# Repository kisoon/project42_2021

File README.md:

# project42_2021
42보드 지원 문서에 오신 것을 환영합니다! 여기에서 사용 방법에 대한 정보를 찾을 수 있습니다.<br>
프로젝트 42 피지컬 컴퓨팅 키트 <a href=https://github.com/kisoon/project42_2021> 온라인 자료(깃허브)</a>

-- <a href = https://github.com/kisoon/project42_2021#-%EC%84%A4%EC%B9%98-%EB%B0%A9%EB%B2%95-> 보드 설치방법 </a><br>
-- <a href = https://github.com/kisoon/project42_2021/blob/main/README.md#-%EB%9D%BC%EC%9D%B4%EB%B8%8C%EB%9F%AC%EB%A6%AC-%EC%84%A4%EC%B9%98-%EB%B0%A9%EB%B2%95->라이브러리 설치 방법 </a> <br>
-- <a href = https://github.com/kisoon/project42_2021/blob/main/5-2.%20%ED%95%A8%EA%BB%98%20%EC%82%AC%EC%9A%A9%ED%95%98%EA%B8%B0.md> 함께사용하기 </a>

<H3> 보드 설치 방법 </h3>
1. 아두이노 프로그램을 설치해주세요. https://www.arduino.cc/en/software 다음 링크에서 자신의 컴퓨터OS환경에 맞는 버전을 다운로드 받으면 됩니다.<br>

2. 아두이노 프로그램을 실행시키고 환경설정 윈도우를 열어주세요.<br>
   win:파일->환경설정(Ctrl+,) / mac:arduino->preference(Command+,)<br>
   
3. 그리고 사진의 주황색 칸에 다음 링크를 복사하여 붙여넣고 확인버튼(OK)을 눌러주세요
   https://raw.githubusercontent.com/espressif/arduino-esp32/gh-pages/package_esp32_index.json<br>
4. 아두이노에서 보드 매니저를 실행하세요. 도구(Tools) 메뉴 -> Board -> 보드 매니저(Board Manager)
<br>
5. 보드 매니저를 실행 후 esp32 라고 검색을 해주세요. 그리고, <b>1.0.6버전</b>을 선택하고, 설치(instll)버튼을 클릭하여 esp32 보드를 아두이노에 설치합니다.

6. 그리고 아두이노 IDE를 다시 실행시키세요.

7. 다시! 도구(Tools) 메뉴 -> Board에서 ESP32 Arduino -> ESP32 Dev Module을 선택합니다.
  
8. 마지막으로 자신의 컴퓨터의 설치된 42보드 포트를 선택해야합니다. 포트를 선택하기전 컴퓨터에 드라이버 소프트웨어를 설치합니다.
   42보드에는 cp2104라는 USB포트 인식 칩이 내장되어 있습니다.
   다음 링크에서 자신의 컴퓨터 환경에 맞는 드라이버를 다운받아 설치합니다.
   https://www.silabs.com/developers/usb-to-uart-bridge-vcp-drivers

9. 드라이버의 설치를 완료한 뒤 다시 아두이노 IDE로 돌아와 도구(Tools) 메뉴에서 port를 확인합니다. 42보드를 USB케이블로 컴퓨터와 연결하면, 자신의 컴퓨터에 설치된 42보드 포트를 확인할 수 있습니다.
    windows는 COM[숫자]의 형태로 되어있습니다.

10. 42보드를 사용할 때는 항상 보드이름과 포트를 확인 후 사용합니다.

<H3> 라이브러리 설치 방법 </h3>
아두이노 라이브러리 설치 가이드 -> https://www.arduino.cc/en/Guide/Libraries

1. 라이브러리는 아두이노 IDE를 실행하여 설치할 수 있다.<br>
2. 스케치 메뉴 -> 라이브러리 포함하기(include library) -> Manage libraries를 선택한다.<br>

3. 검색창에 다음 라이브러리를 검색한 후 모두 설치를 한다.
   1) Adafruit_MPR121
   2) MPU6050 by electronic cats https://github.com/electroniccats/mpu6050
   3) Adafruit neopixel https://github.com/adafruit/Adafruit_NeoPixel
4. 다운받은 폴더의 libraries안의 AsyncTCP 폴더와 ESPAsyncWebServer 폴더를 <br>문서 -> arduino -> libraries 폴더안에 붙여넣기 합니다.<br>

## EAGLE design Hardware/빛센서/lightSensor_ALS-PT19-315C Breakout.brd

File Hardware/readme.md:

1. 42키트는 오픈소스를 활용해 만들었습니다.
2. autodesk eagle cad를 이용해 하드웨어를 디자인하였습니다.
3. https://www.autodesk.com/products/eagle/overview

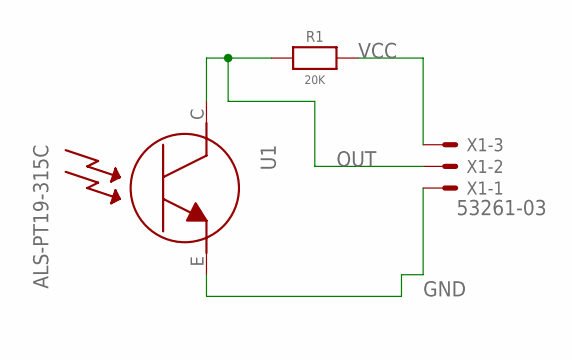
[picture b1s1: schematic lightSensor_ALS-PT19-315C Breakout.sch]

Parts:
R1: 20K; 0603-NO
U1: ALS-PT19-315C
X1: 53261-03

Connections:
GND: U1.E, X1.1
OUT: R1.2, U1.C, X1.2
VCC: R1.1, X1.3

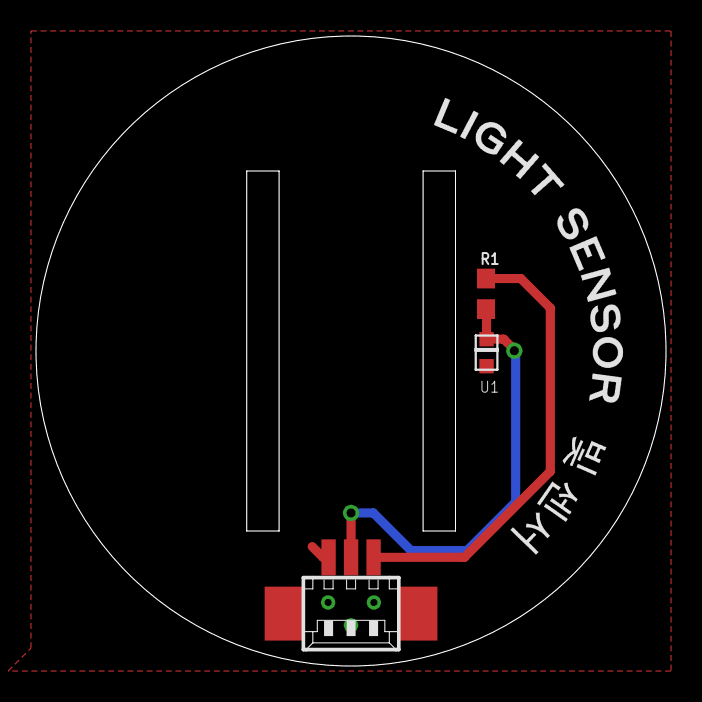
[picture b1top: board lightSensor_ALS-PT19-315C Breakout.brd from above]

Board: 2 copper layers, 35.0 x 35.0 mm, 3 parts (0 on the bottom side), 3 nets.

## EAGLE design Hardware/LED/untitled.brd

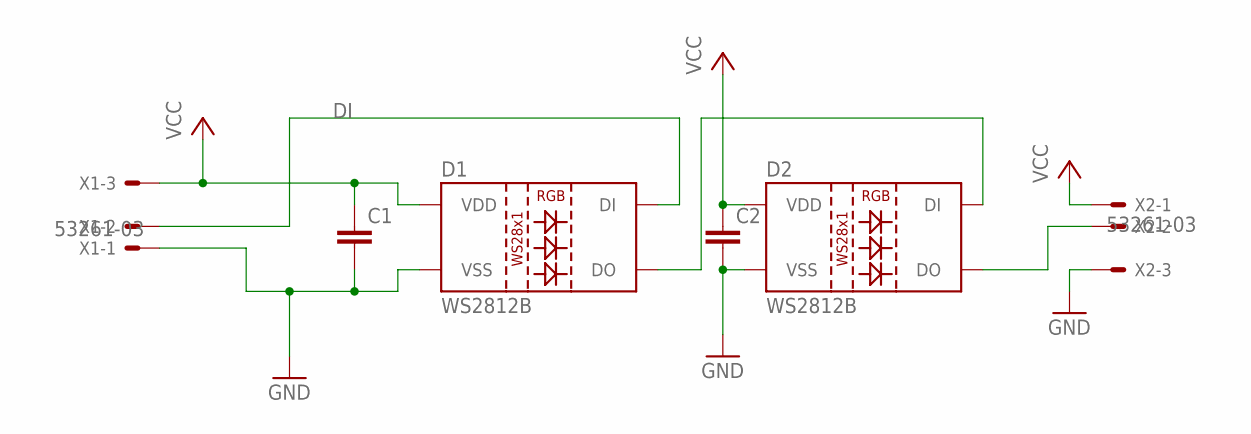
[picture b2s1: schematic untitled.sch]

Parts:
C1, C2: C-EUC0603; C0603
D1, D2: WS2812B
X1, X2: 53261-03

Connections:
DI: D1.4 (DI), X1.2
GND: C1.2, C2.2, D1.3 (VSS), D2.3 (VSS), X1.1, X2.3
unnamed: D2.2 (DO), X2.2
unnamed: D1.2 (DO), D2.4 (DI)
VCC: C1.1, C2.1, D1.1 (VDD), D2.1 (VDD), X1.3, X2.1

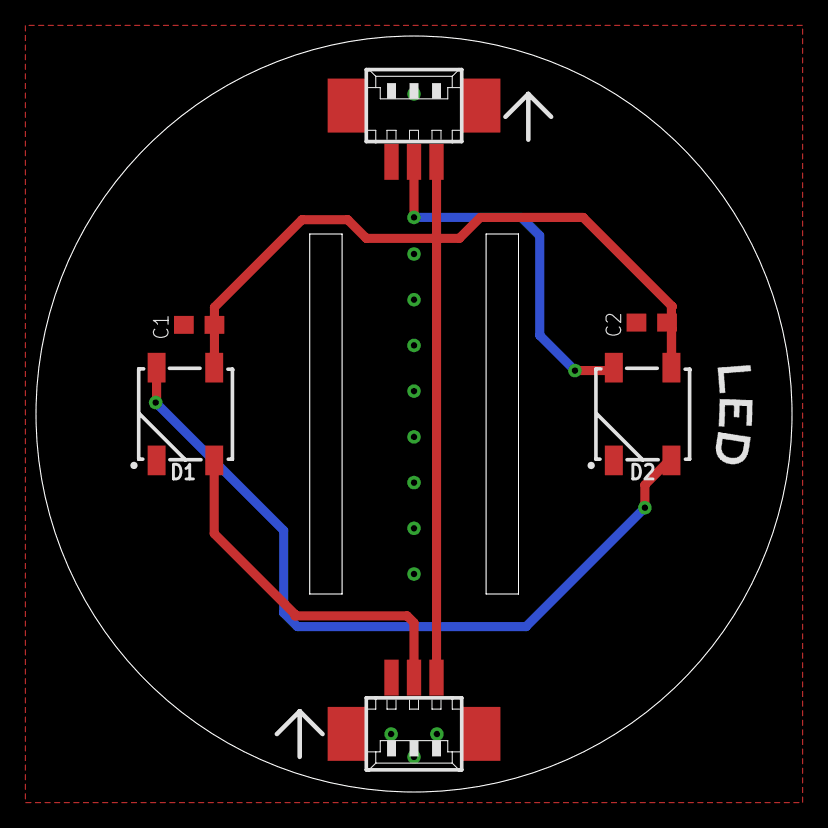
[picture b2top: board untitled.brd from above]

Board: 2 copper layers, 42.0 x 42.0 mm, 6 parts (0 on the bottom side), 5 nets.

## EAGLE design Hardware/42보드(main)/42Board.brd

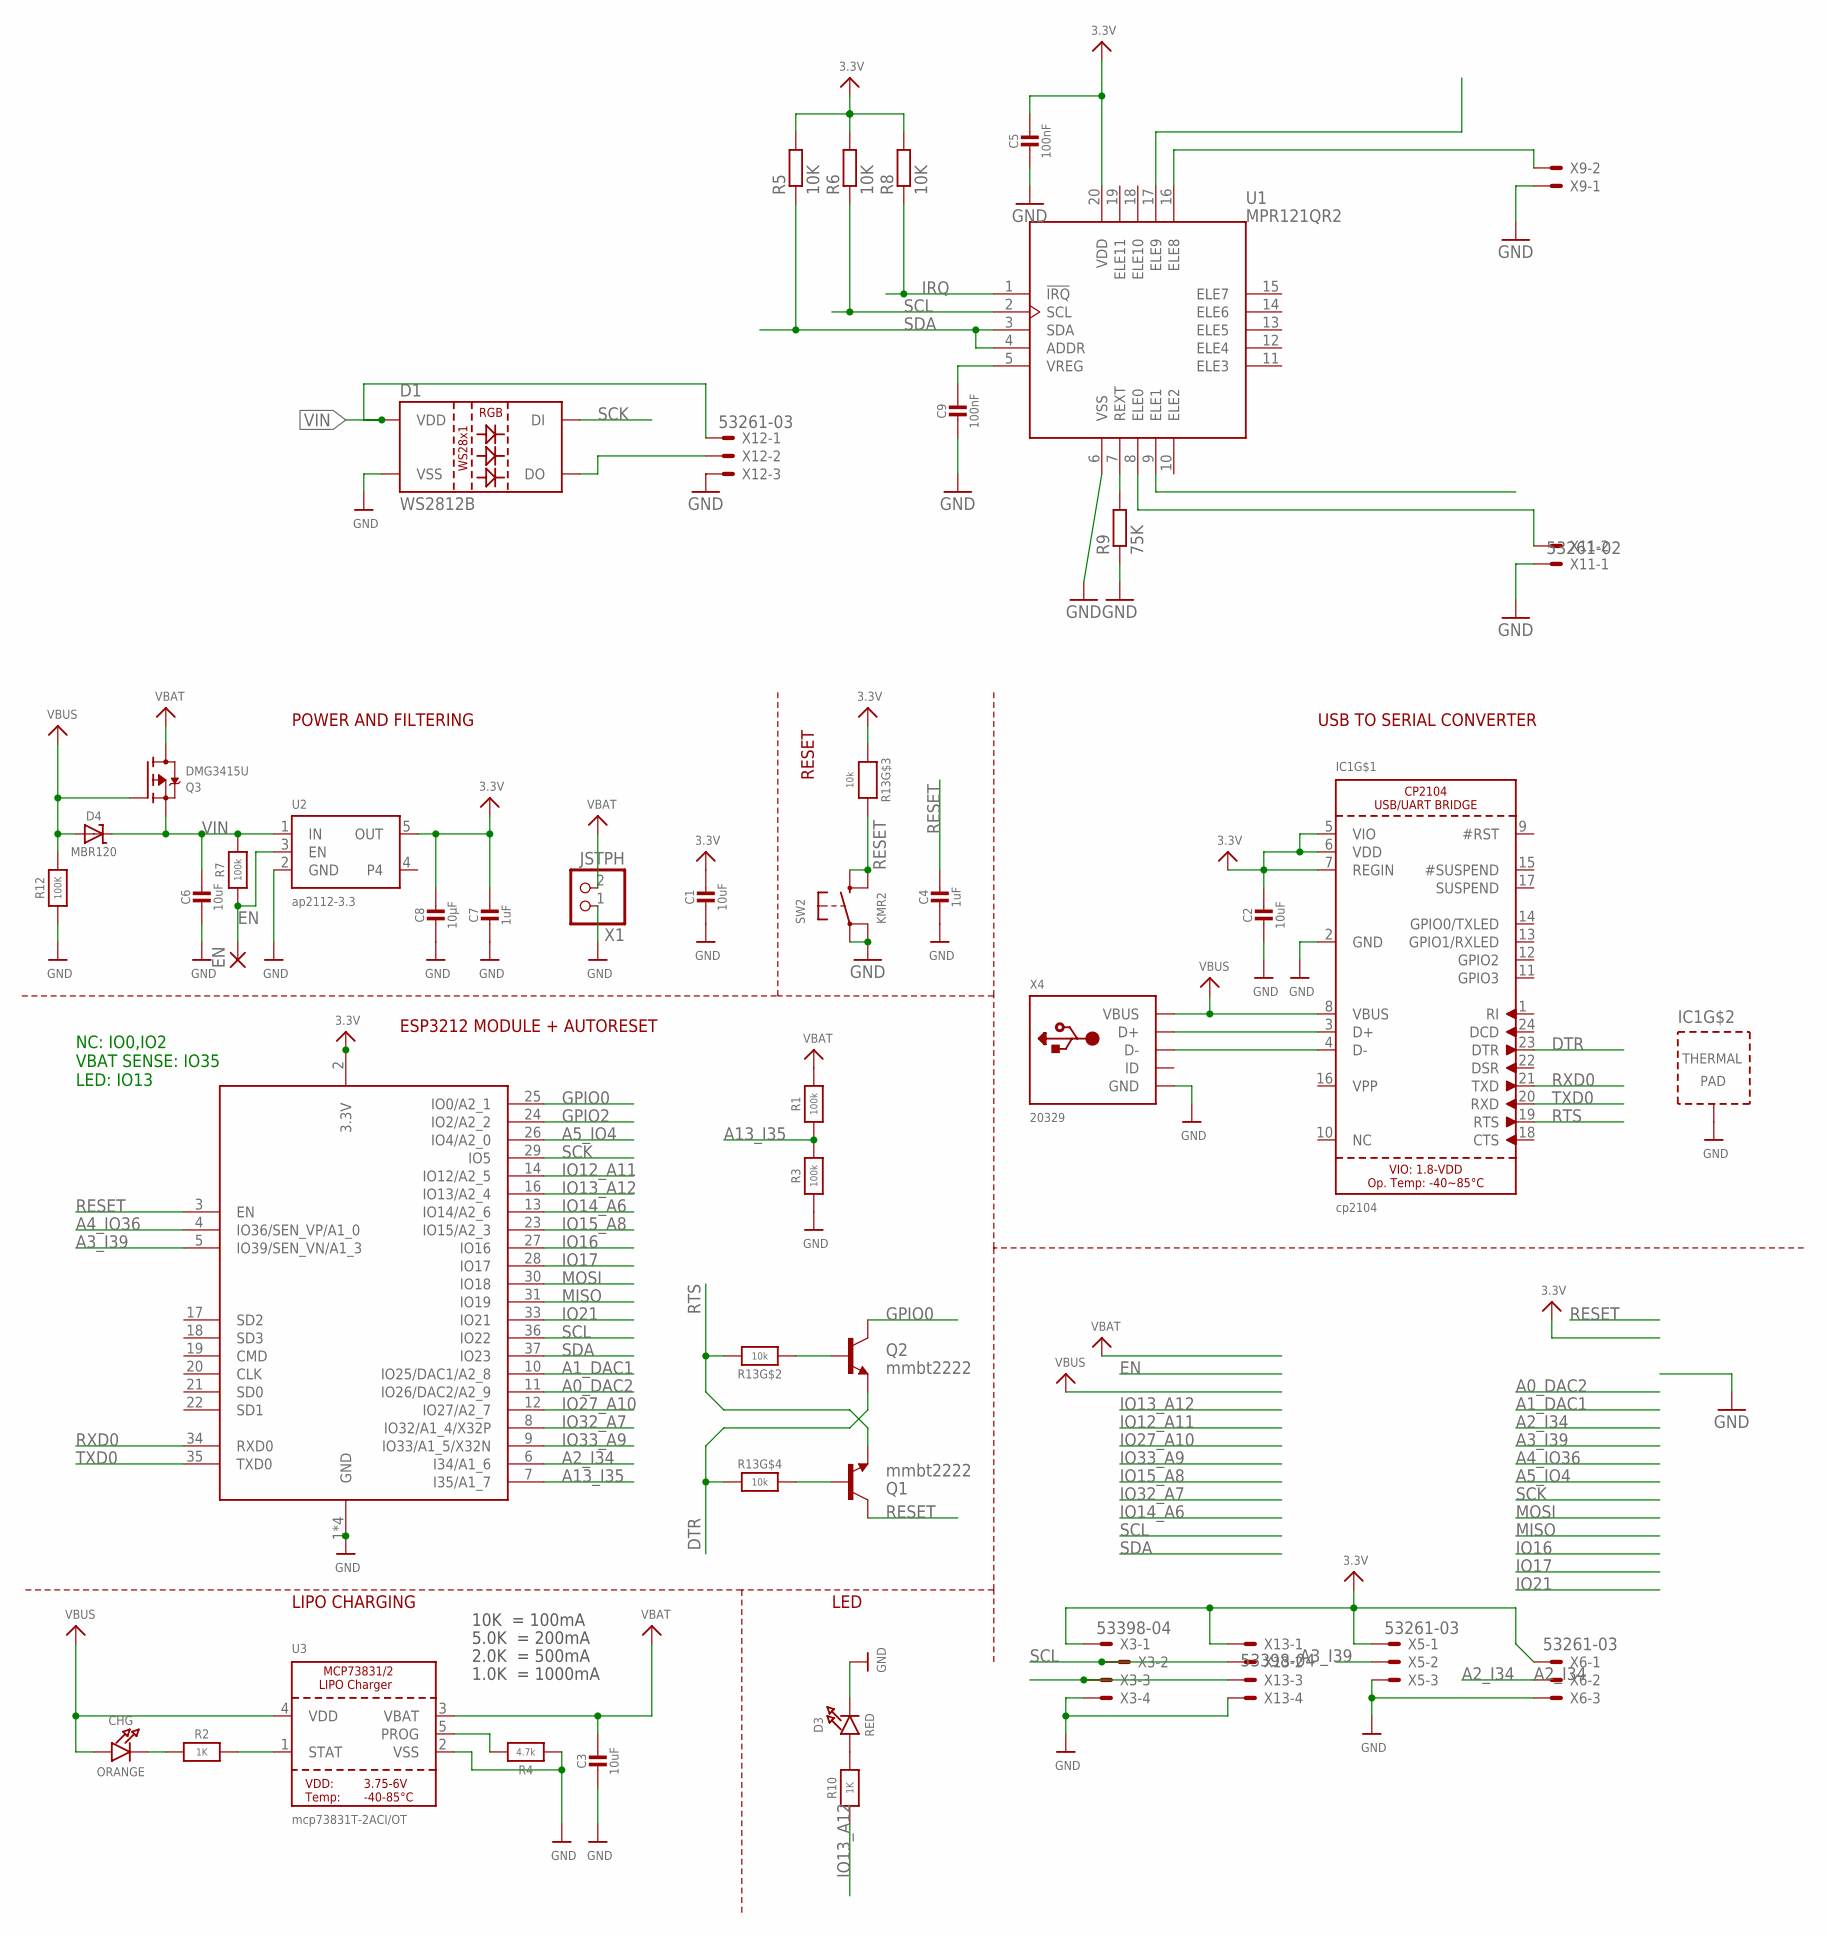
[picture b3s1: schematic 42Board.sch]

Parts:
C1, C2, C3, C6: 10uF; 0805-NO
C4, C7: 1uF; 0603-NO
C5, C9: 100nF; 0603-NO
C8: 10µF; 0805-NO
CHG: ORANGE; CHIPLED_0805_NOOUTLINE
D1: WS2812B
D3: RED; CHIPLED_0805_NOOUTLINE
D4: MBR120; SOD-123
EN: 1,6/0,8
IC1: cp2104; QFN24_4MM_SMSC
Q1, Q2: mmbt2222; SOT23-3
Q3: DMG3415U; SOT23-R
R1, R3, R7: 100k; 0603-NO
R2, R10: 1K; 0603-NO
R4: 4.7k; 0603-NO
R5, R6, R8: 10K; R0603
R9: 75K; R0603
R12: 100K; 0603-NO
R13: 10k; RESPACK_4X0603
SW2: KMR2; BTN_KMR2_4.6X2.8
U1: MPR121QR2; UFQFN-20
U2: ap2112-3.3; SOT23-5
U3: mcp73831T-2ACI/OT; SOT23-5
X1: JSTPH; JSTPH2
X2: ESP32_WROOM32_SKINNY; WROOM32_SKINNY
X3, X13: 53398-04
X4: 20329; 4UCONN_20329_V2
X5, X6, X12: 53261-03
X9, X11: 53261-02

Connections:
3.3V: C1.1, C2.1, C5.1, C7.1, C8.1, IC1.5 (VIO), IC1.6 (VDD), IC1.7 (REGIN), R5.2, R6.2, R8.2, R13.3 (1), U1.20 (VDD), U2.5 (OUT), X2.2 (3.3V), X3.1, X5.1, X6.1, X13.1
A0_DAC2: X2.11 (IO26/DAC2/A2_9)
A1_DAC1: X2.10 (IO25/DAC1/A2_8)
A2_I34: X2.6 (I34/A1_6), X6.2
A3_I39: X2.5 (IO39/SEN_VN/A1_3), X5.2
A4_IO36: X2.4 (IO36/SEN_VP/A1_0)
A5_IO4: X2.26 (IO4/A2_0)
A13_I35: R1.1, R3.2, X2.7 (I35/A1_7)
DTR: IC1.23 (DTR), Q2.2 (E), R13.4 (1)
EN: EN.1, R7.1, U2.3 (EN)
GND: C1.2, C2.2, C3.2, C4.2, C5.2, C6.2, C7.2, C8.2, C9.2, D1.3 (VSS), D3.C, IC1.2 (GND), IC1.THERM (TP), R3.1, R4.1, R9.1, R12.1, SW2.A, SW2.A' (P1), U1.6 (VSS), U2.2 (GND), U3.2 (VSS), X1.1, X2.1 (GND), X2.15 (GND), X2.38 (GND), X2.P$1 (GND), X3.4, X4.BASE@1 (GND), X4.BASE@2 (GND), X4.GND, X4.SPRT@1 (GND), X4.SPRT@2 (GND), X4.SPRT@3 (GND), X4.SPRT@4 (GND), X5.3, X6.3, X9.1, X11.1, X12.3, X13.4
GPIO0: Q2.3 (C), X2.25 (IO0/A2_1)
GPIO2: X2.24 (IO2/A2_2)
IO12_A11: X2.14 (IO12/A2_5)
IO13_A12: R10.1, X2.16 (IO13/A2_4)
IO14_A6: X2.13 (IO14/A2_6)
IO15_A8: X2.23 (IO15/A2_3)
IO16: X2.27 (IO16)
IO17: X2.28 (IO17)
IO21: X2.33 (IO21)
IO27_A10: X2.12 (IO27/A2_7)
IO32_A7: X2.8 (IO32/A1_4/X32P)
IO33_A9: X2.9 (IO33/A1_5/X32N)
IRQ: R8.1, U1.1 (!IRQ)
MISO: X2.31 (IO19)
MOSI: X2.30 (IO18)
unnamed: CHG.C, R2.1
unnamed: IC1.3 (D+), X4.D+
unnamed: R2.2, U3.1 (STAT)
unnamed: R4.2, U3.5 (PROG)
unnamed: D3.A, R10.2
unnamed: IC1.4 (D-), X4.D-
unnamed: D1.2 (DO), X12.2
unnamed: R9.2, U1.7 (REXT)
unnamed: U1.8 (ELE0), X11.2
unnamed: C9.1, U1.5 (VREG)
unnamed: Q1.1 (B), R13.5 (2)
unnamed: Q2.1 (B), R13.2 (1)
unnamed: U1.16 (ELE8), X9.2
RESET: C4.1, Q1.3 (C), R13.6 (2), SW2.B (S), SW2.B' (S1), X2.3 (EN)
RTS: IC1.19 (RTS), Q1.2 (E), R13.7 (2)
RXD0: IC1.21 (TXD), X2.34 (RXD0)
SCK: D1.4 (DI), X2.29 (IO5)
SCL: R6.1, U1.2 (SCL), X2.36 (IO22), X3.2, X13.2
SDA: R5.1, U1.3 (SDA), U1.4 (ADDR), X2.37 (IO23), X3.3, X13.3
TXD0: IC1.20 (RXD), X2.35 (TXD0)
VBAT: C3.1, Q3.3 (D), R1.2, U3.3 (VBAT), X1.2
VBUS: CHG.A, D4.A, IC1.8 (VBUS), Q3.1 (G), R12.2, U3.4 (VDD), X4.VBUS
VIN: C6.1, D1.1 (VDD), D4.C, Q3.2 (S), R7.2, U2.1 (IN), X12.1

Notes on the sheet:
POWER AND FILTERING
RESET
10K = 100mA
5.0K = 200mA
2.0K = 500mA
1.0K = 1000mA
USB TO SERIAL CONVERTER
LIPO CHARGING
LED
ESP3212 MODULE + AUTORESET
NC: IO0,IO2 VBAT SENSE: IO35 LED: IO13

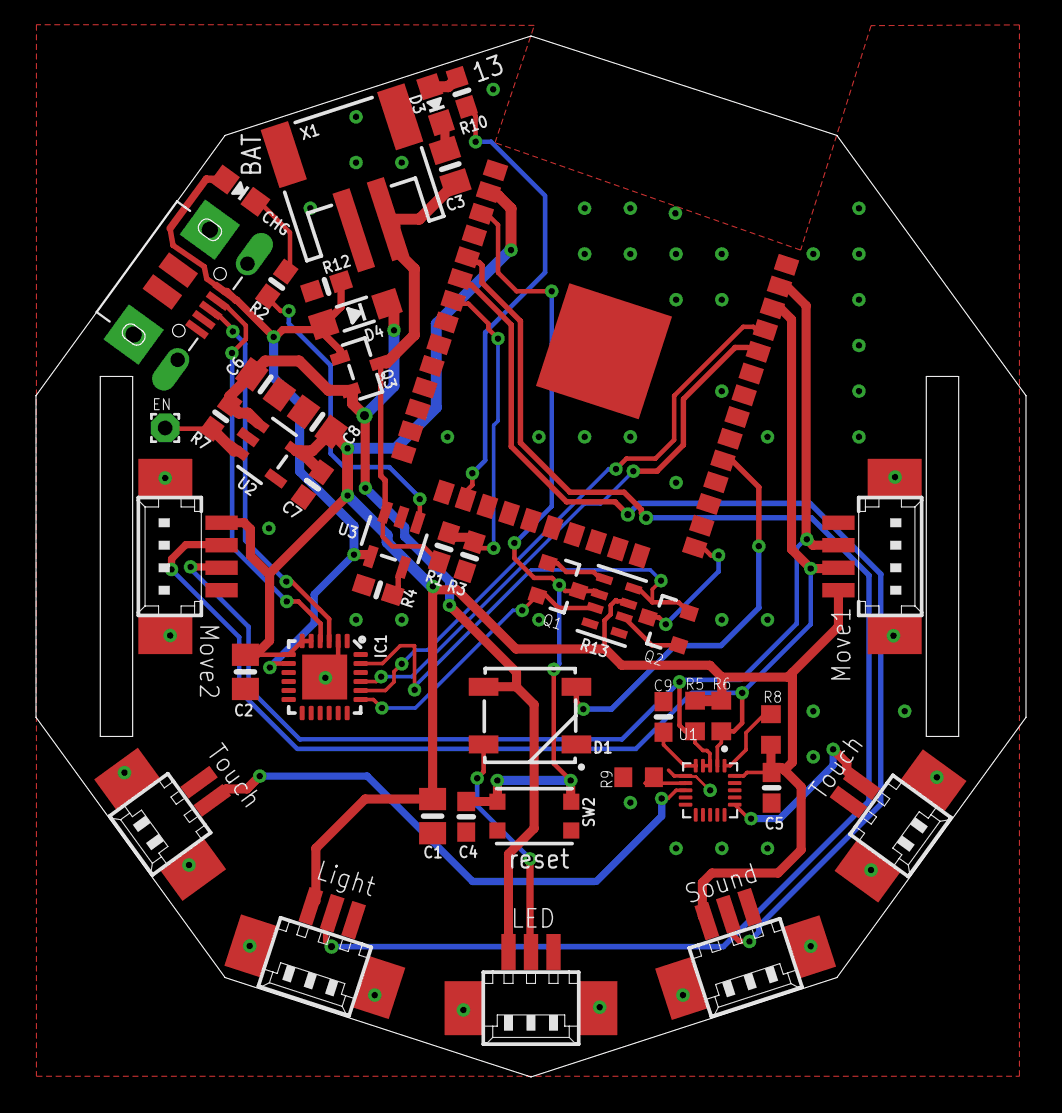
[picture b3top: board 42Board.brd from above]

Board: 2 copper layers, 55.0 x 57.8 mm, 44 parts (0 on the bottom side), 33 nets.

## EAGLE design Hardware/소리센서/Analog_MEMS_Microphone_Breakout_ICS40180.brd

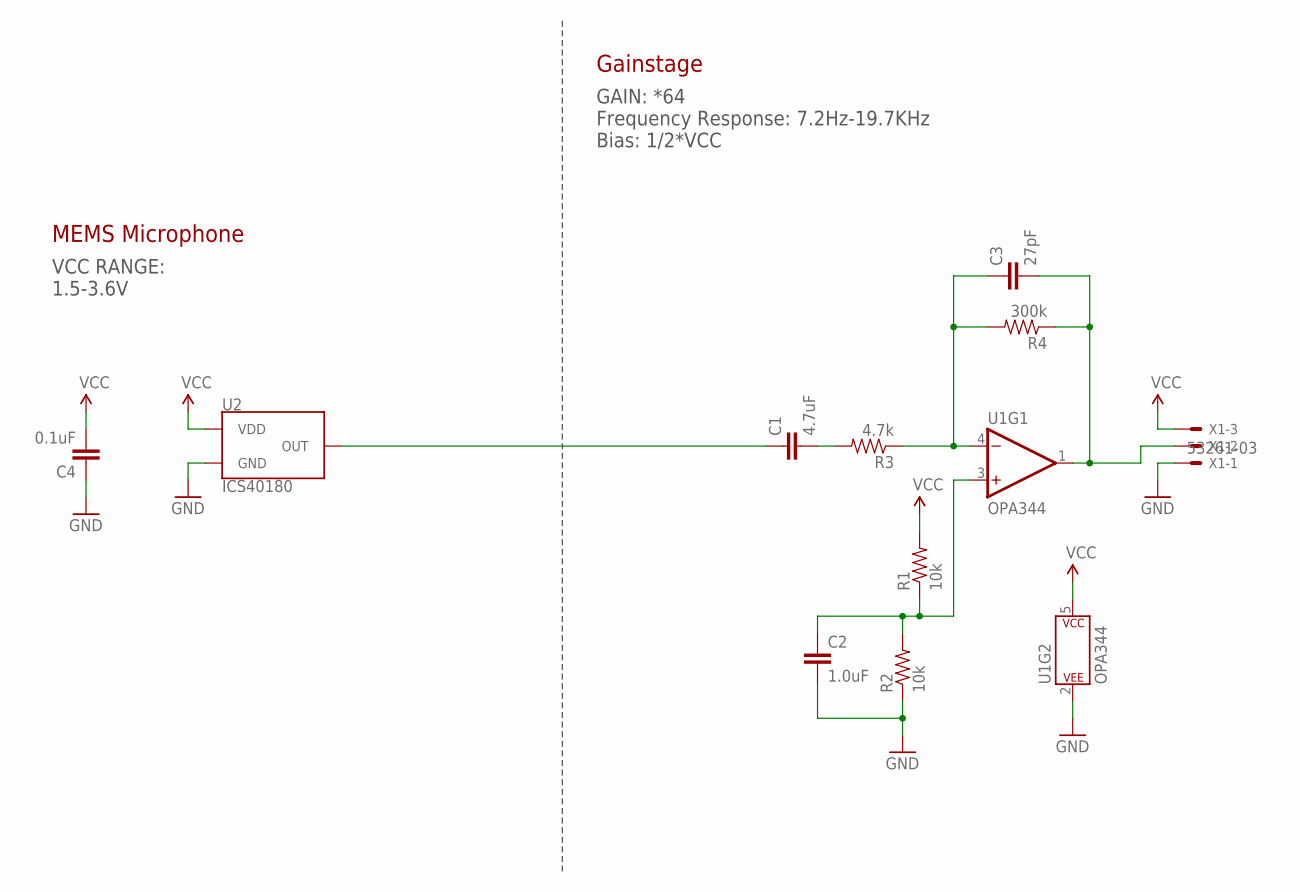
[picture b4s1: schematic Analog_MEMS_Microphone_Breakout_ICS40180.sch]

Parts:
C1: 4.7uF; 0603
C2: 1.0uF; 0603
C3: 27pF; 0603
C4: 0.1uF; 0603
R1, R2: 10k; 0603
R3: 4.7k; 0603
R4: 300k; 0603
U1: OPA344; SOT23-5
U2: ICS40180
X1: 53261-03

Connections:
AUD: C3.2, R4.1, U1.1 (OUT), X1.2
GND: C2.2, C4.1, R2.1, U1.2 (P$V-), U2.2 (GND), U2.3 (GND), U2.4 (GND), X1.1
unnamed: C1.1, U2.1 (OUT)
unnamed: C3.1, R3.1, R4.2, U1.4 (-IN)
unnamed: C1.2, R3.2
unnamed: C2.1, R1.1, R2.2, U1.3 (+IN)
VCC: C4.2, R1.2, U1.5 (P$V+), U2.5 (VDD), X1.3

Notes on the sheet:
VCC RANGE: 1.5-3.6V
MEMS Microphone
Gainstage
GAIN: *64 Frequency Response: 7.2Hz-19.7KHz Bias: 1/2*VCC

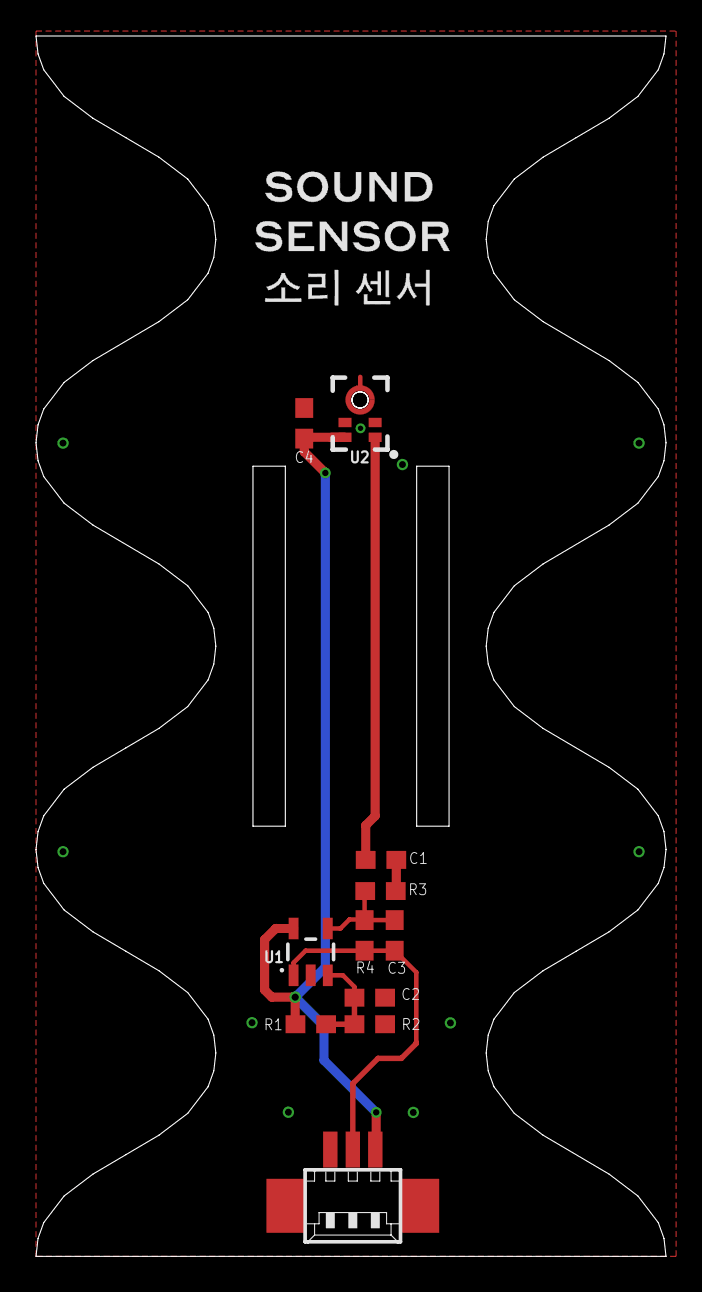
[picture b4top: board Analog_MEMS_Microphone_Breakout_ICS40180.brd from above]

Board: 2 copper layers, 35.0 x 67.8 mm, 11 parts (0 on the bottom side), 7 nets.

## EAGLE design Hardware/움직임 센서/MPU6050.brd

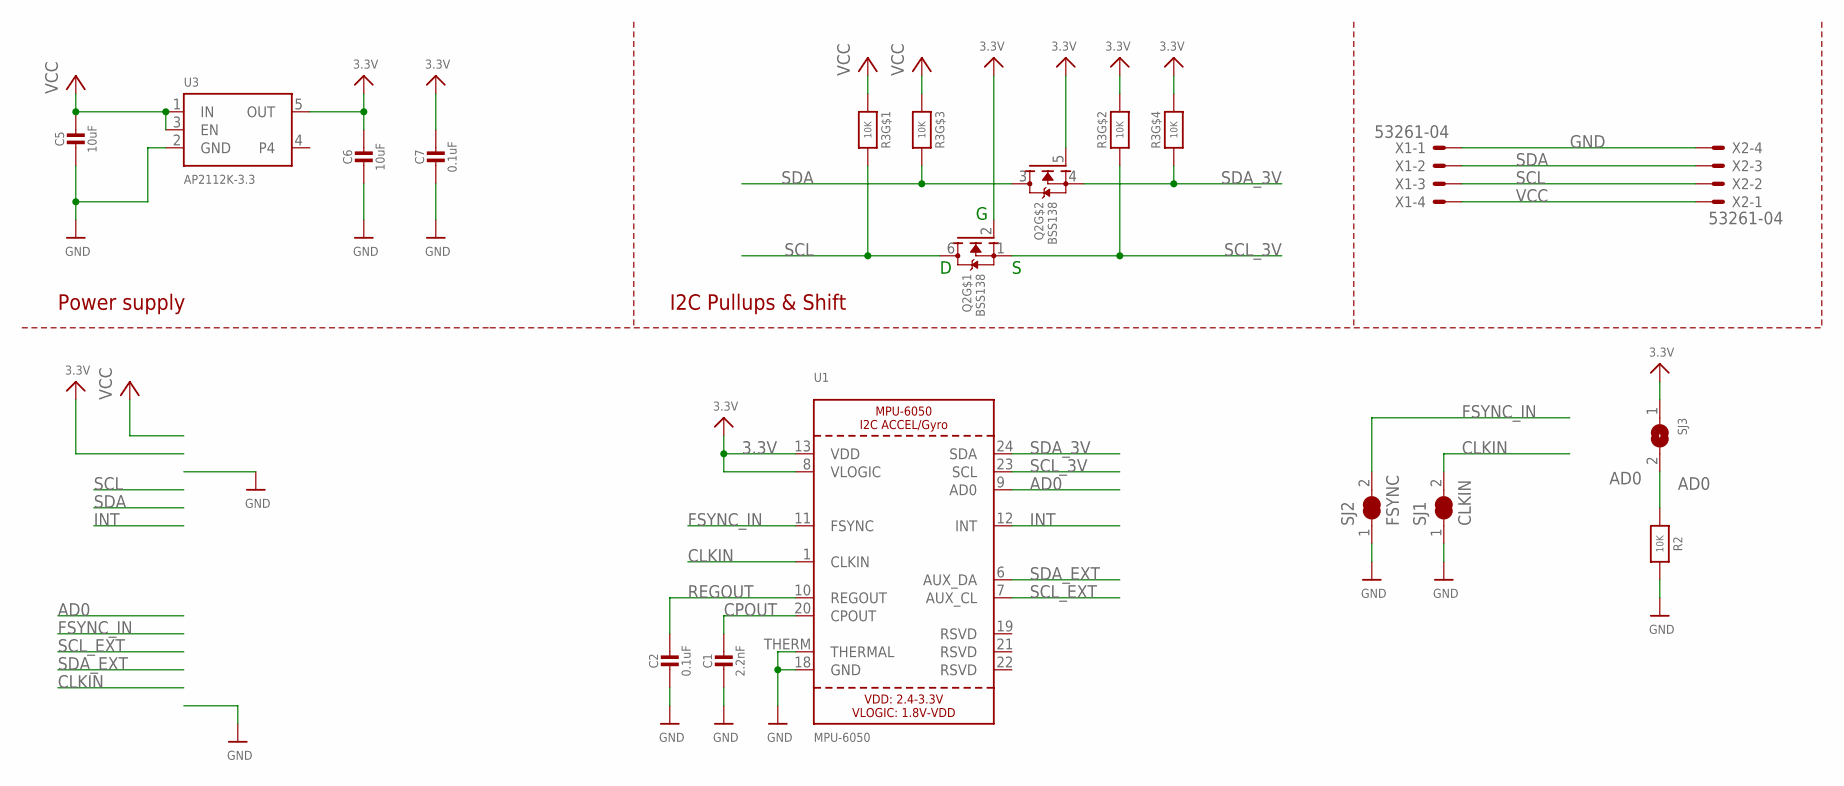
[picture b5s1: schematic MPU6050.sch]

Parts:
C1: 2.2nF; 0603-NO
C2, C7: 0.1uF; 0603-NO
C5, C6: 10uF; 0805-NO
Q2: BSS138; SOT363
R2: 10K; 0603-NO
R3: 10K; RESPACK_4X0603
SJ1: CLKIN; SOLDERJUMPER_CLOSEDWIRE
SJ2: FSYNC; SOLDERJUMPER_CLOSEDWIRE
SJ3: SOLDERJUMPER; SOLDERJUMPER_ARROW_NOPASTE
U1: MPU-6050; QFN24_4MM_SMSC
U3: AP2112K-3.3; SOT23-5
X1, X2: 53261-04

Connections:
3.3V: C6.1, C7.1, Q2.2 (G), Q2.5 (G), R3.2 (1), R3.4 (1), SJ3.1, U1.8 (VLOGIC), U1.13 (VDD), U3.5 (OUT)
AD0: R2.1, SJ3.2, U1.9 (AD0)
CLKIN: SJ1.2, U1.1 (CLKIN)
CPOUT: C1.1, U1.20 (CPOUT)
FSYNC_IN: SJ2.2, U1.11 (FSYNC)
GND: C1.2, C2.2, C5.2, C6.2, C7.2, R2.2, SJ1.1, SJ2.1, U1.18 (GND), U1.THERM (THERMAL), U3.2 (GND), X1.1, X2.4
INT: U1.12 (INT)
REGOUT: C2.1, U1.10 (REGOUT)
SCL: Q2.6 (D), R3.8 (2), X1.3, X2.2
SCL_3V: Q2.1 (S), R3.7 (2), U1.23 (SCL)
SCL_EXT: U1.7 (AUX_CL)
SDA: Q2.3 (D), R3.6 (2), X1.2, X2.3
SDA_3V: Q2.4 (S), R3.5 (2), U1.24 (SDA)
SDA_EXT: U1.6 (AUX_DA)
VCC: C5.1, R3.1, R3.3 (1), U3.1 (IN), U3.3 (EN), X1.4, X2.1

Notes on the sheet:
I2C Pullups & Shift
Power supply

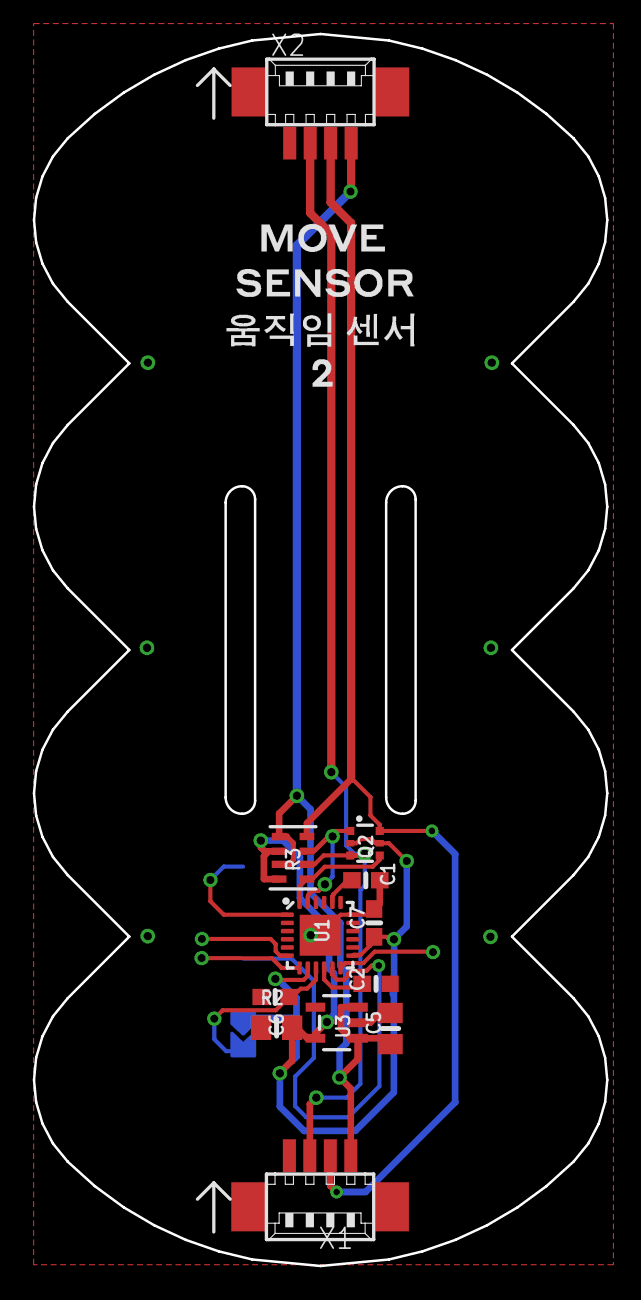
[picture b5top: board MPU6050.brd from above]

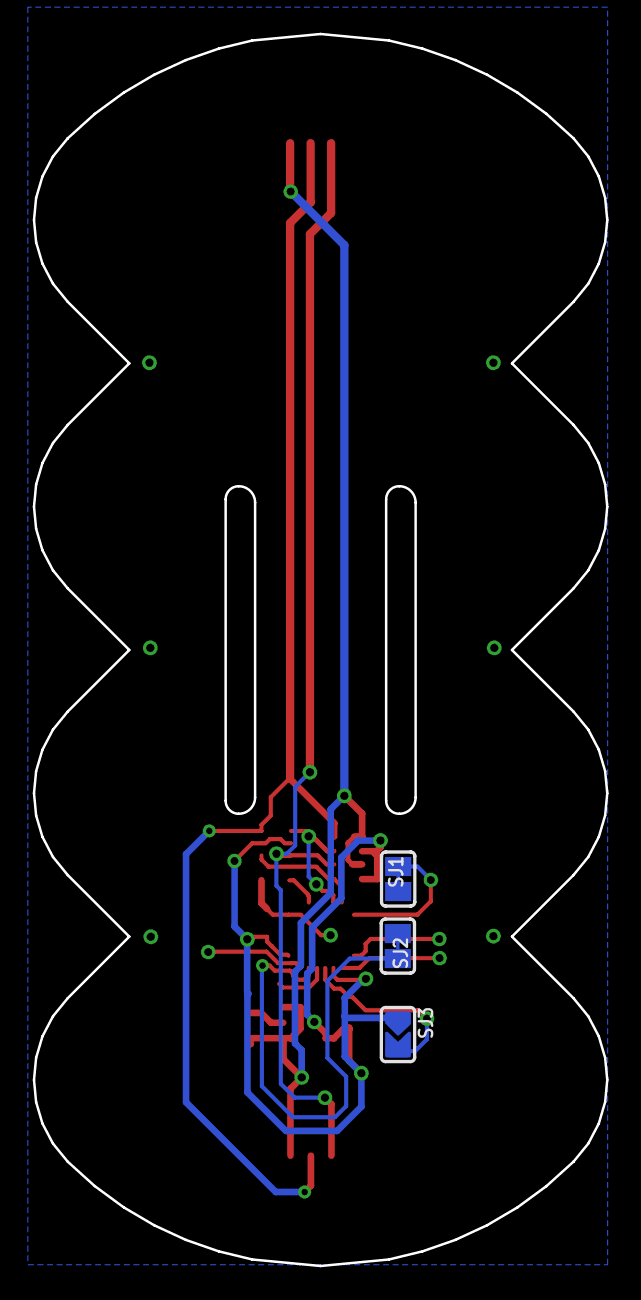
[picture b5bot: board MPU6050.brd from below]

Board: 2 copper layers, 35.0 x 75.2 mm, 15 parts (3 on the bottom side), 12 nets.

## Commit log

2021-07-02 Create 42board Sketch code
2021-08-04 Create 함께 사용하기
2021-08-04 Rename 함께 사용하기 to 함께 사용하기.md
2021-08-04 Rename 함께 사용하기.md to 5-2. 함께 사용하기.md

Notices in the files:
parts and their libraries:
microbuilder: This work is placed in the public domain, and may be freely used for commercial and non-commercial work with the following conditions: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
SparkFun: Licensing: CC v3.0 Share-Alike You are welcome to use this library for commercial purposes.
